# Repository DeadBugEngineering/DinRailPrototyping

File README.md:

# DinRailPrototyping
A collection of information and designs to accelerate the creation of custom electronics that fit into a DIN rail chassis

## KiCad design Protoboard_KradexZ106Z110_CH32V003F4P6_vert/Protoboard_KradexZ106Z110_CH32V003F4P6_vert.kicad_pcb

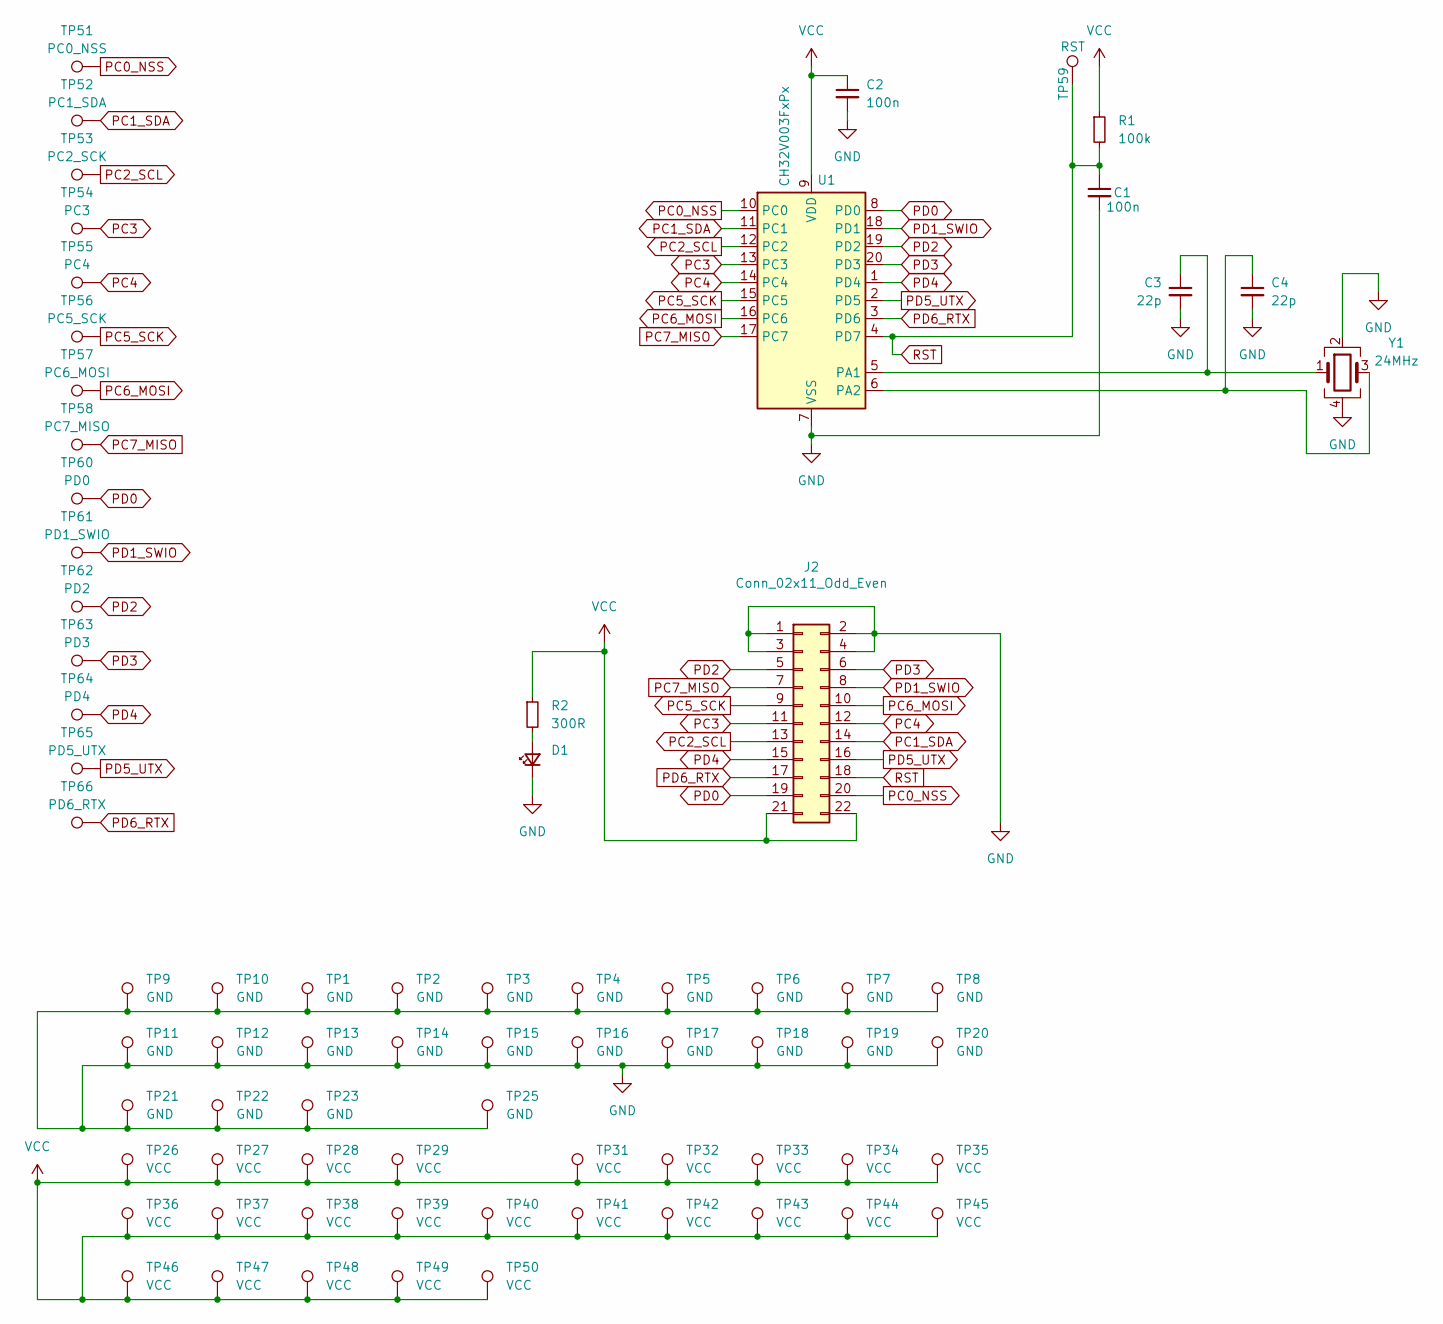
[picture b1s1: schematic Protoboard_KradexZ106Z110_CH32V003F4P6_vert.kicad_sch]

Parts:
C1, C2: 100n; C_0805_2012Metric_Pad1.18x1.45mm_HandSolder
C3, C4: 22p; C_0805_2012Metric_Pad1.18x1.45mm_HandSolder
D1: PowerGood; LED_0805_2012Metric_Pad1.15x1.40mm_HandSolder
J2: Conn_02x11_Odd_Even; PinHeader_2x11_P2.54mm_Horizontal
R1: 100k; R_0805_2012Metric_Pad1.20x1.40mm_HandSolder
R2: 300R; R_0805_2012Metric_Pad1.20x1.40mm_HandSolder
TP1, TP2, TP3, TP4, TP5, TP6, TP7, TP8, TP9, TP10, TP11, TP12, TP13, TP14, TP15, TP16, TP17, TP18, TP19, TP20, TP21, TP22, TP23, TP25: GND; TestPoint_THTPad_D2.0mm_Drill1.0mm
TP26, TP27, TP28, TP29, TP31, TP32, TP33, TP34, TP35, TP36, TP37, TP38, TP39, TP40, TP41, TP42, TP43, TP44, TP45, TP46, TP47, TP48, TP49, TP50: VCC; TestPoint_THTPad_D2.0mm_Drill1.0mm
TP51: PC0_NSS; TestPoint_THTPad_D1.0mm_Drill0.5mm
TP52: PC1_SDA; TestPoint_THTPad_D1.0mm_Drill0.5mm
TP53: PC2_SCK; TestPoint_THTPad_D1.0mm_Drill0.5mm
TP54: PC3; TestPoint_THTPad_D1.0mm_Drill0.5mm
TP55: PC4; TestPoint_THTPad_D1.0mm_Drill0.5mm
TP56: PC5_SCK; TestPoint_THTPad_D1.0mm_Drill0.5mm
TP57: PC6_MOSI; TestPoint_THTPad_D1.0mm_Drill0.5mm
TP58: PC7_MISO; TestPoint_THTPad_D1.0mm_Drill0.5mm
TP59: RST; TestPoint_THTPad_D1.0mm_Drill0.5mm
TP60: PD0; TestPoint_THTPad_D1.0mm_Drill0.5mm
TP61: PD1_SWIO; TestPoint_THTPad_D1.0mm_Drill0.5mm
TP62: PD2; TestPoint_THTPad_D1.0mm_Drill0.5mm
TP63: PD3; TestPoint_THTPad_D1.0mm_Drill0.5mm
TP64: PD4; TestPoint_THTPad_D1.0mm_Drill0.5mm
TP65: PD5_UTX; TestPoint_THTPad_D1.0mm_Drill0.5mm
TP66: PD6_RTX; TestPoint_THTPad_D1.0mm_Drill0.5mm
U1: CH32V003FxPx; TSSOP-20_4.4x6.5mm_P0.65mm
Y1: 24MHz; Crystal_SMD_3225-4Pin_3.2x2.5mm

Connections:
GND: C1.2, C2.2, C3.2, C4.2, D1.1 (K), J2.1, J2.2, J2.3, J2.4, TP1.1, TP2.1, TP3.1, TP4.1, TP5.1, TP6.1, TP7.1, TP8.1, TP9.1, TP10.1, TP11.1, TP12.1, TP13.1, TP14.1, TP15.1, TP16.1, TP17.1, TP18.1, TP19.1, TP20.1, TP21.1, TP22.1, TP23.1, TP25.1, U1.7 (VSS), Y1.2, Y1.4
unnamed: D1.2 (A), R2.2
unnamed: C3.1, U1.5 (PA1), Y1.1
unnamed: C4.1, U1.6 (PA2), Y1.3
PC0_NSS: J2.20, TP51.1, U1.10 (PC0)
PC1_SDA: J2.14, TP52.1, U1.11 (PC1)
PC2_SCL: J2.13, TP53.1, U1.12 (PC2)
PC3: J2.11, TP54.1, U1.13 (PC3)
PC4: J2.12, TP55.1, U1.14 (PC4)
PC5_SCK: J2.9, TP56.1, U1.15 (PC5)
PC6_MOSI: J2.10, TP57.1, U1.16 (PC6)
PC7_MISO: J2.7, TP58.1, U1.17 (PC7)
PD0: J2.19, TP60.1, U1.8 (PD0)
PD1_SWIO: J2.8, TP61.1, U1.18 (PD1)
PD2: J2.5, TP62.1, U1.19 (PD2)
PD3: J2.6, TP63.1, U1.20 (PD3)
PD4: J2.15, TP64.1, U1.1 (PD4)
PD5_UTX: J2.16, TP65.1, U1.2 (PD5)
PD6_RTX: J2.17, TP66.1, U1.3 (PD6)
RST: C1.1, J2.18, R1.2, TP59.1, U1.4 (PD7)
VCC: C2.1, J2.21, J2.22, R1.1, R2.1, TP26.1, TP27.1, TP28.1, TP29.1, TP31.1, TP32.1, TP33.1, TP34.1, TP35.1, TP36.1, TP37.1, TP38.1, TP39.1, TP40.1, TP41.1, TP42.1, TP43.1, TP44.1, TP45.1, TP46.1, TP47.1, TP48.1, TP49.1, TP50.1, U1.9 (VDD)

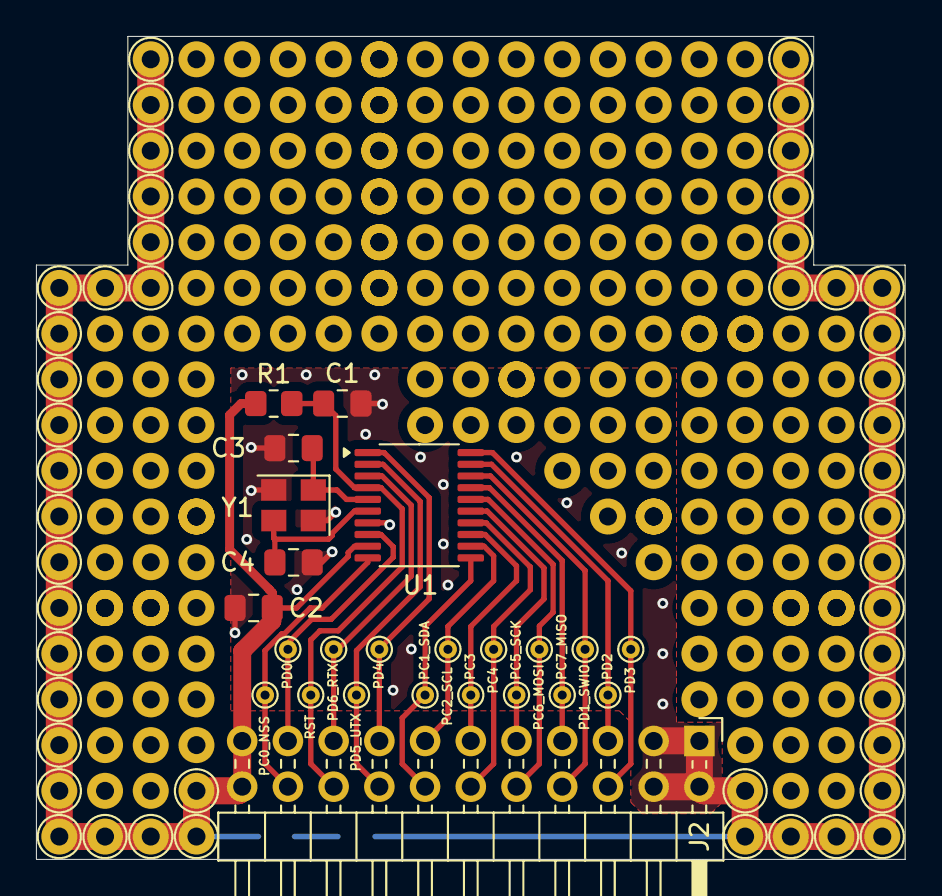
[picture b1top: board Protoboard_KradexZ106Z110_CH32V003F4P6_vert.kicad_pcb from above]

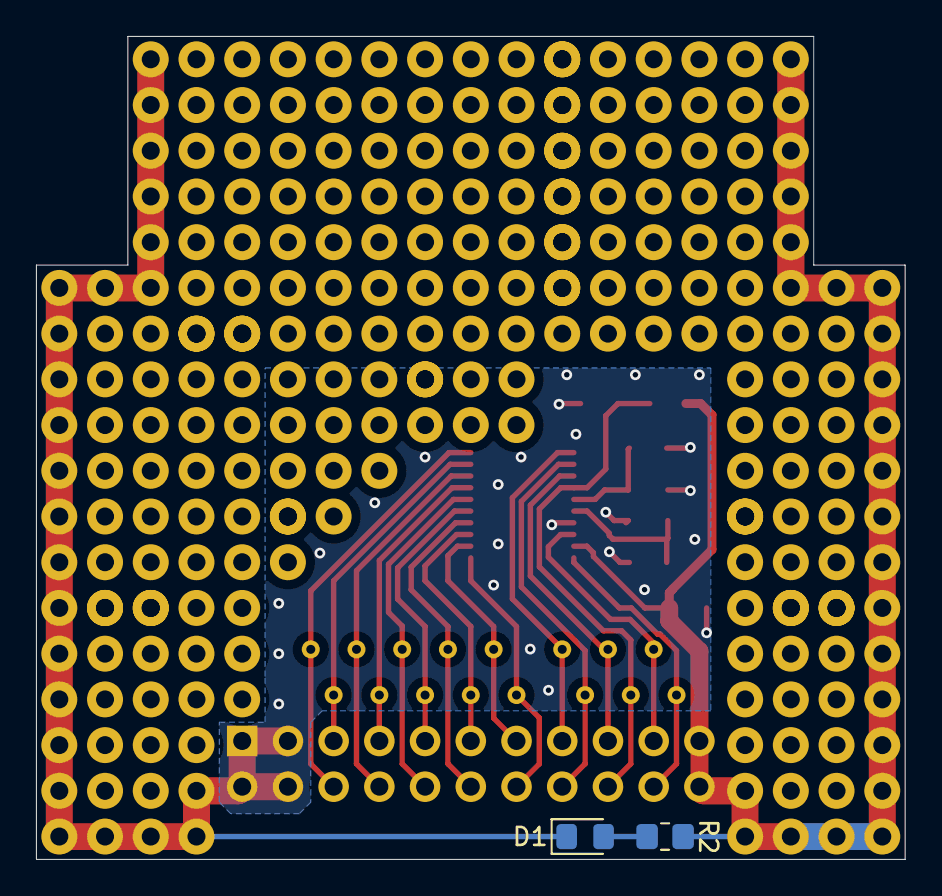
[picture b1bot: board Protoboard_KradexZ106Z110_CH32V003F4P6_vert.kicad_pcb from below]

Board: 2 copper layers, 48.3 x 45.7 mm, 74 parts (2 on the bottom side), 21 nets.

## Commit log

2024-09-19 added boards after verifying mechanical fit
